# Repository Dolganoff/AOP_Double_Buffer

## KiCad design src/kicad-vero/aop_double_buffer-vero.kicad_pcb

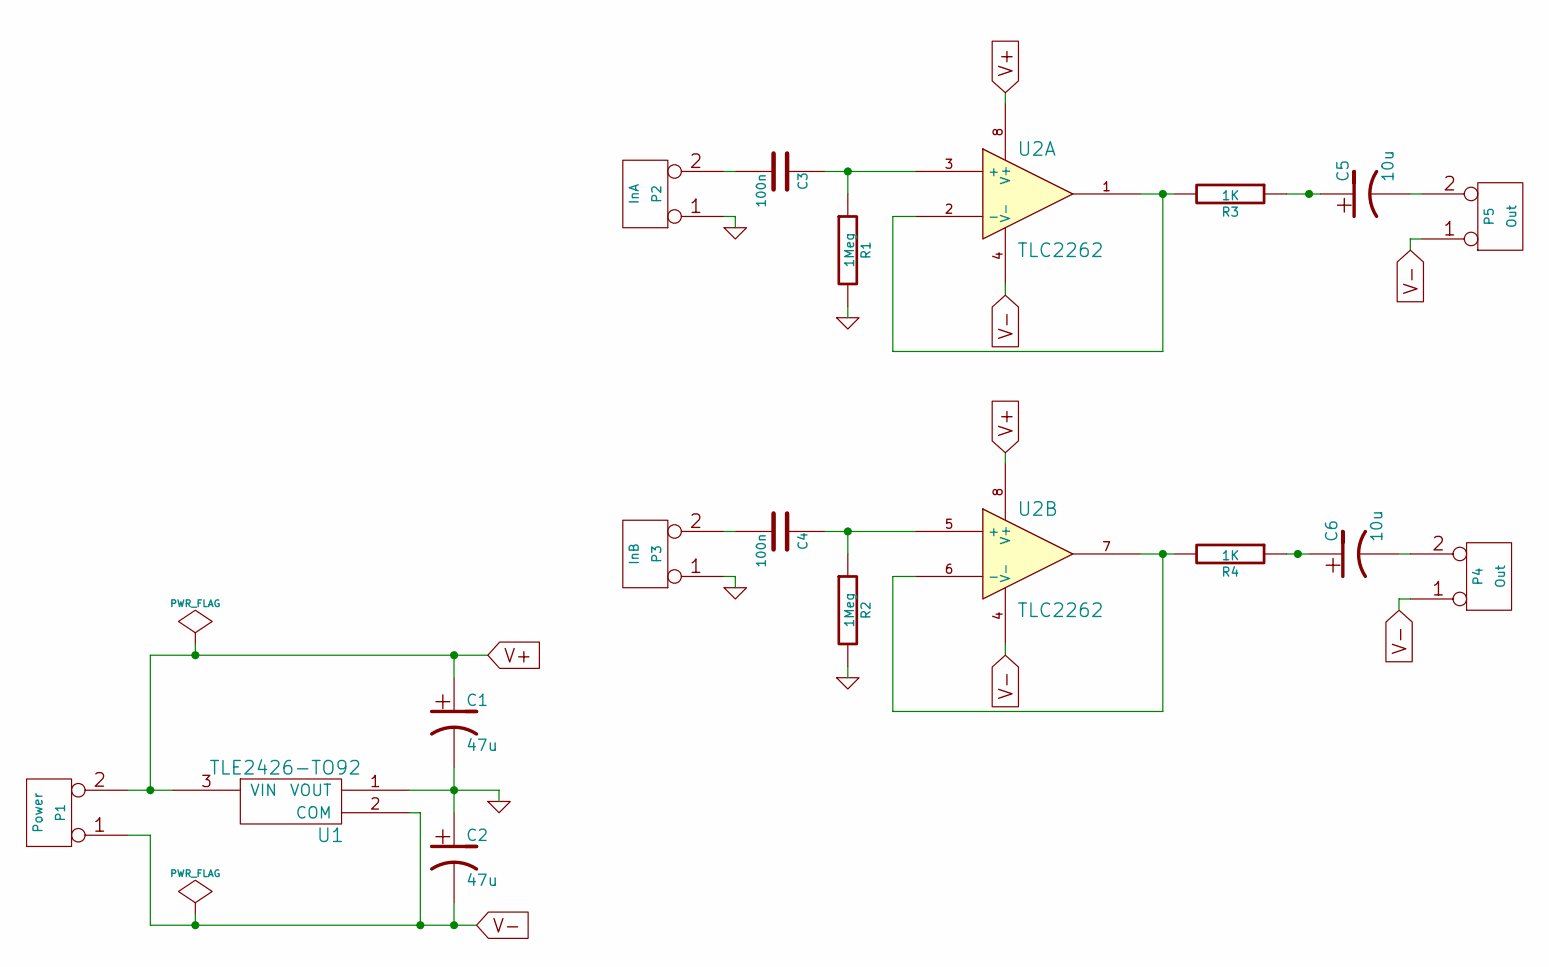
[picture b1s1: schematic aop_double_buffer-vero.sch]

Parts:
C1, C2: 47u; C1V5-LARGE_PADS
C3, C4: 100n; C2-LARGE_PADS
C5, C6: 10u; C1V5-LARGE_PADS
P1: Power; SIL-2-LARGE_PADS
P2: InA; SIL-2-LARGE_PADS
P3: InB; SIL-2-LARGE_PADS
P4, P5: Out; SIL-2-LARGE_PADS
R1, R2: 1Meg; R3-LARGE_PADS
R3, R4: 1K; R3-LARGE_PADS
U1: TLE2426-TO92; TO-92-Free-rugged
U2: TLC2262; DIP-8_LARGE_PADS

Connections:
GND: C1.2, C2.1, P2.1, P3.1, R1.2, R2.2, U1.1 (VOUT)
unnamed: C3.1, R1.1, U2.3 (+)
unnamed: C3.2, P2.2 (PM)
unnamed: C4.1, R2.1, U2.5 (+)
unnamed: C4.2, P3.2 (PM)
unnamed: C5.1, R3.1
unnamed: C5.2, P5.2 (PM)
unnamed: C6.1, R4.1
unnamed: C6.2, P4.2 (PM)
unnamed: R3.2, U2.1, U2.2 (-)
unnamed: R4.2, U2.6 (-), U2.7
V+: C1.1, P1.2 (PM), U1.3 (VIN), U2.8 (V+)
V-: C2.2, P1.1, P4.1, P5.1, U1.2 (COM), U2.4 (V-)

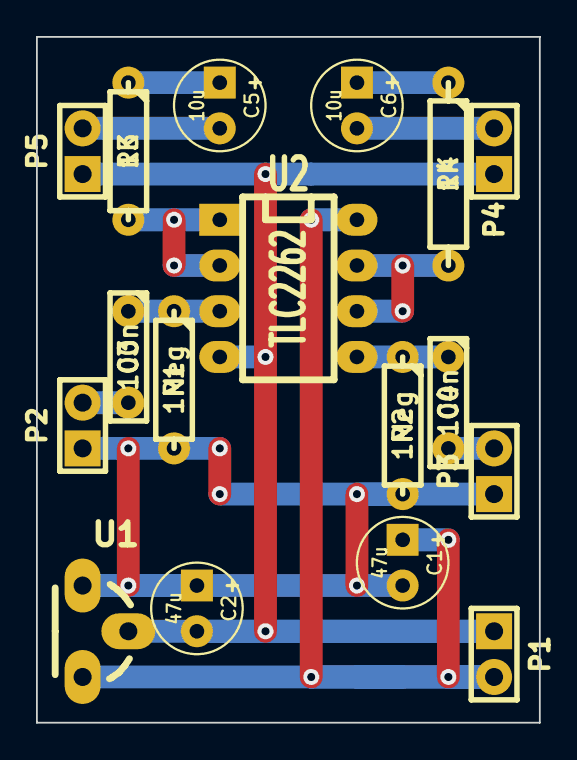
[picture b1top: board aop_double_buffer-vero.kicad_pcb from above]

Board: 2 copper layers, 27.9 x 38.1 mm, 24 parts (0 on the bottom side), 13 nets.

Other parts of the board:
o: track_drill
o#2, o#3, o#4, o#5, o#6, o#7: track_drill

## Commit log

2015-01-11 :tada: Added .gitattributes & .gitignore files
2015-01-17 finalisation
